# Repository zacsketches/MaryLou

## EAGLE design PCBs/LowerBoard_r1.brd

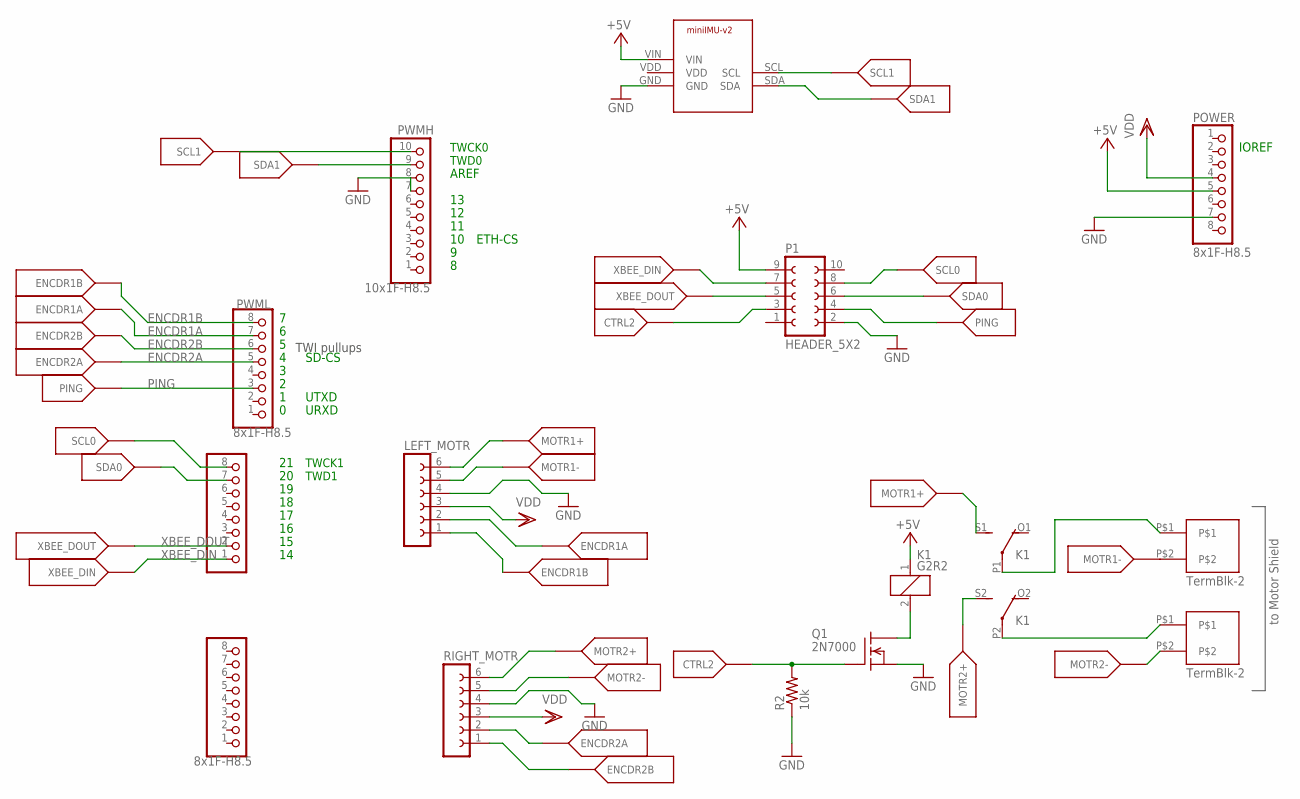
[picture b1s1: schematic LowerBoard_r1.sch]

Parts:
ANALOG: 8x1F-H8.5; 1X08
COMMS: PINHD-1X8; 1X08
K1: G2R2
LEFT_MOTR: FE06-1; FE06
P1: HEADER_5X2
POWER: 8x1F-H8.5; 1X08
PWMH: 10x1F-H8.5; 1X10
PWML: 8x1F-H8.5; 1X08
Q1: 2N7000; TO92
R2: 10k; RESISTOR_PKG
RIGHT_MOTR: FE06-1; FE06
U$5: POLOLU_MINIIMU9_V2; POLOLU_IMU9V2
U$11: motor1; TB2_PKG
U$12: TB2; TB2_PKG

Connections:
+5V: K1.1, P1.9, POWER.5, U$5.VIN
CTRL2: P1.3, Q1.G, R2.2
ENCDR1A: LEFT_MOTR.2, PWML.7
ENCDR1B: LEFT_MOTR.1, PWML.8
ENCDR2A: PWML.5, RIGHT_MOTR.2
ENCDR2B: PWML.6, RIGHT_MOTR.1
GND: LEFT_MOTR.4, P1.2, POWER.7, PWMH.7, Q1.S, R2.1, RIGHT_MOTR.4, U$5.GND
MOTR1+: K1.S1 (S), LEFT_MOTR.6
MOTR1-: LEFT_MOTR.5, U$11.P$2
MOTR2+: K1.S2 (S), RIGHT_MOTR.6
MOTR2-: RIGHT_MOTR.5, U$12.P$2
unnamed: K1.P1, U$11.P$1
unnamed: K1.P2, U$12.P$1
unnamed: K1.2, Q1.D
PING: P1.4, PWML.3
SCL: PWMH.10, U$5.SCL
SCL0: COMMS.8, P1.8
SDA: PWMH.9, U$5.SDA
SDA0: COMMS.7, P1.6
VDD: LEFT_MOTR.3, POWER.4, RIGHT_MOTR.3
XBEE_DIN: COMMS.1, P1.7
XBEE_DOUT: COMMS.2, P1.5

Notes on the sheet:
TWI pullups
TWCK1
TWD1
IOREF
TWCK0
TWD0
AREF
SD-CS
UTXD
URXD
ETH-CS
to Motor Shield

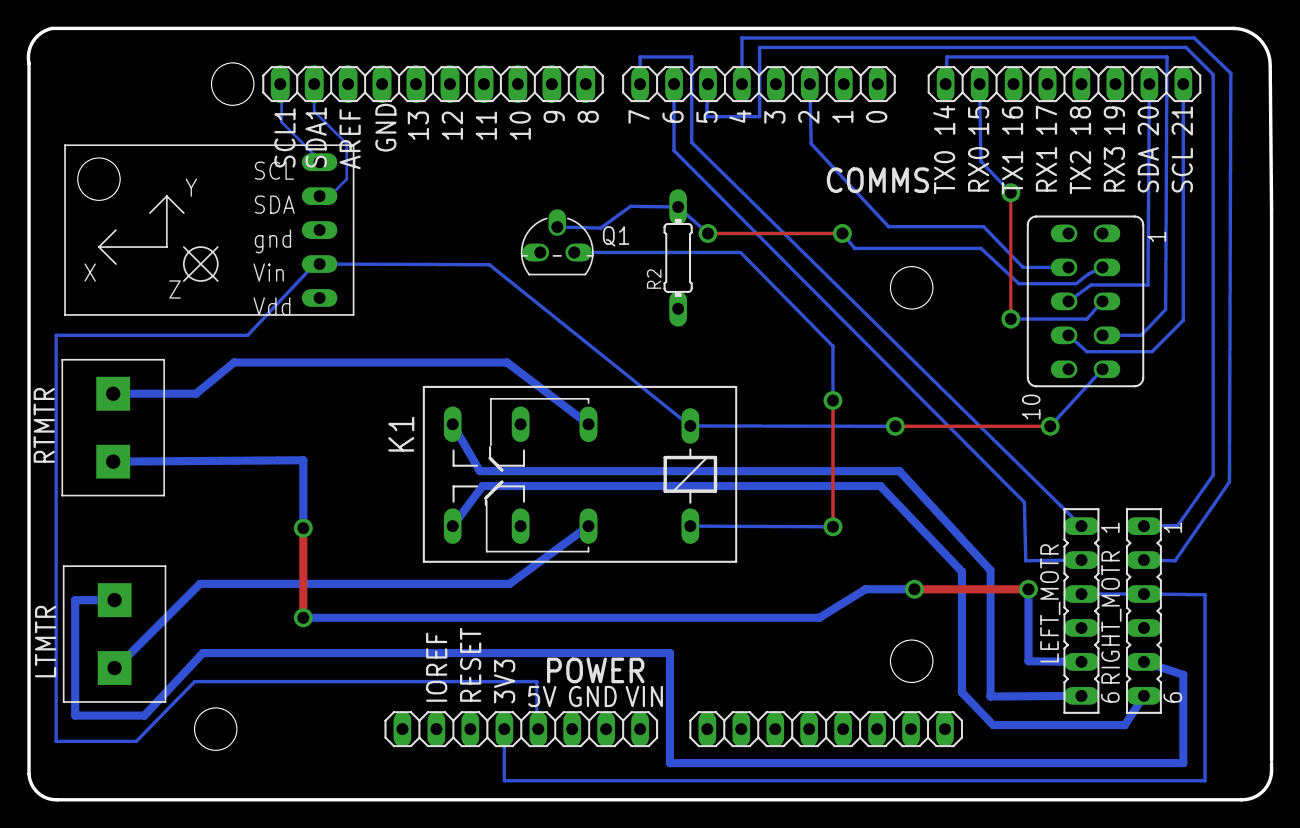
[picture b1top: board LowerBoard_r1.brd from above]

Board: 2 copper layers, 93.0 x 57.7 mm, 15 parts (0 on the bottom side), 22 nets.

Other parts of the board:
DRILEGEND: DRILEGEND

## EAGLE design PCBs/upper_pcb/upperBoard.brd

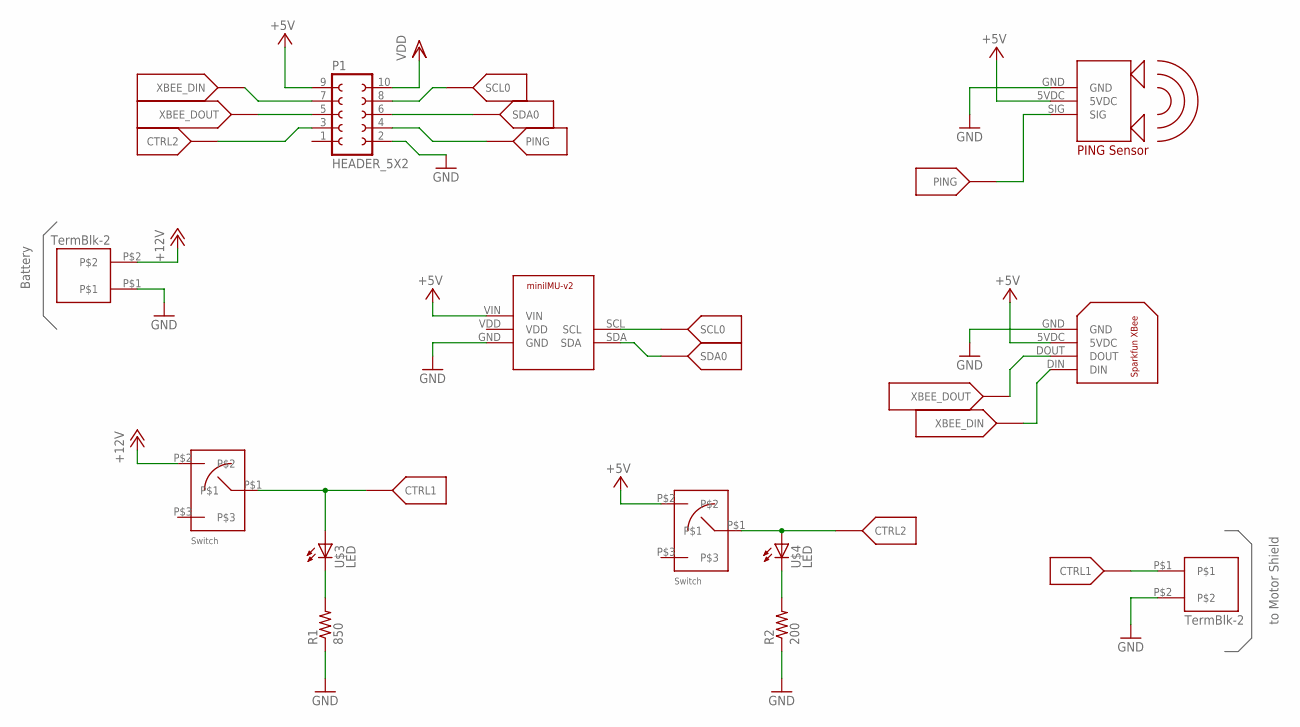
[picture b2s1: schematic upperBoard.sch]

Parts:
P1: HEADER_5X2
R1: 850; RESISTOR_PKG
R2: 200; RESISTOR_PKG
U$1, U$2: SWITCH-SPST
U$3, U$4: LED; LED_PKG
U$7: POLOLU_MINIIMU9_V2; POLOLU_IMU9V2
U$8: SPARKFUNXBEE
U$9: PARALLAX_PING; PING
U$16, U$18: TB2; TB2_PKG

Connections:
+5V: P1.9, U$2.P$2, U$7.VIN, U$8.5VDC, U$9.5VDC
+12V: U$1.P$2, U$16.P$2
CTRL1: U$1.P$1, U$3.A, U$18.P$1
CTRL2: P1.3, U$2.P$1, U$4.A
GND: P1.2, R1.1, R2.1, U$7.GND, U$8.GND, U$9.GND, U$16.P$1, U$18.P$2
unnamed: R1.2, U$3.K (C)
unnamed: R2.2, U$4.K (C)
PING: P1.4, U$9.SIG
SCL0: P1.8, U$7.SCL
SDA0: P1.6, U$7.SDA
VDD: P1.10
XBEE_DIN: P1.7, U$8.DIN
XBEE_DOUT: P1.5, U$8.DOUT

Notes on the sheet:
Battery
to Motor Shield

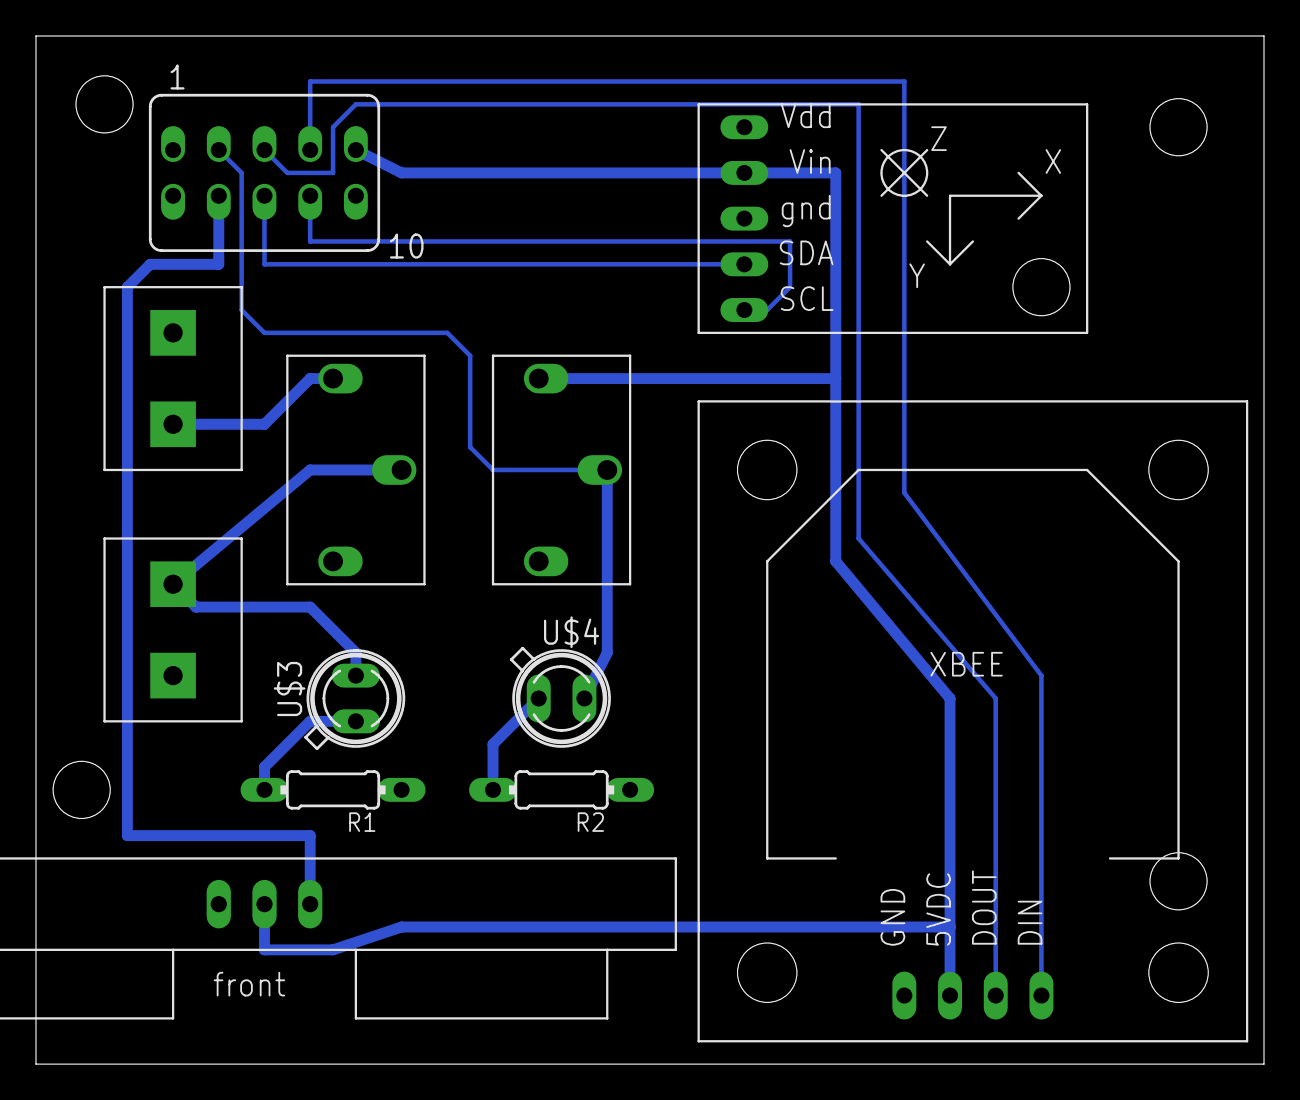
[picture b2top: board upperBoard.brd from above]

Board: 2 copper layers, 68.2 x 57.1 mm, 13 parts (0 on the bottom side), 12 nets.

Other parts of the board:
DRILEGEND: DRILEGEND

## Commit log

2014-10-08 added solidworks files to the project
2014-10-08 added Frame assembly and new Baseplate
    the new Frame assembly includes the mates for
    all the parts. The new Baseplate includes
    the mounting holes for the Neck.
2014-10-09 added table and neck drawing
2014-10-10 Created basic messaging strategy
2014-10-10 Added bill of materials
2014-10-14 major changes
    - Rebuilt file structure to seperate code from physical data
    and reference data
    - Wrote the first code in gyro_test to start working with Pololu
    IMU v2.
2014-10-14 gyro_test compiles...ready for testing e
2014-10-14 added base file for the final robot
2014-10-14 added conv to deg to the gyro test
2014-10-14 Added physical connections
2014-10-14 Added accel .pdf to datasheets
2014-10-15 Added link for IMU info
2014-10-15 Working accelerometer script
2014-10-15 correctd the units to degrees function
2014-10-15 Pitch regulator example added
2014-10-16 compiles...lot's of work still
    - I need to go back into my accel test and change the formula there
    so I get a signed value for pitch. I can't regulate the pitch
    from the gyro until I'm getting like signs from both devices.
2014-10-16 added app note for finding pitch
2014-10-16 used new pitch solution with a signed answer.
2014-10-16 Changed to direct calculation of pitch
    - An important change in this revision, I changed from a
    vector solution to pitch using dot products to a direct
    calculation of pitch using the technique described in
    Freescale App Note 3461.
2014-10-16 Removed unused variables
2014-10-16 Closed issue #1 - adde macro logging
2014-10-16 renamed file to better match its purpose
2014-10-16 Added refs to AN3461 and atan vs atan2
2014-10-16 Yahoo!!! Regulates gyro stability to +/- .3 deg
    - Tuned the PI controller and changed the sign for the
    error signal provide negative feedback.
2014-10-16 Added PI controller tuning reference
2014-10-16 added gyro system diagram to datasheets
2014-10-16 Fine tuned the gyro drift regulator...go with this for now.
2014-10-17 changed phi to theta for pitch variable
2014-10-17 updated System design
2014-10-17 Made a compatibility note at the top of the file
2014-10-17 updated System Design graphic
2014-10-22 working attitude computer
2014-10-22 Updated types for state vector message
2014-10-22 Added state vector process...needs testing
2014-10-23 Working state observer
2014-10-23 added deadband reference to datasheets
2014-10-23 added an MIT thesis on balancing robots and a dedband lab to datasheets
2014-10-23 minor change to LOG macro
2014-10-23 Added another balancing paper to datasheets
2014-10-23 Deadband comp added to the build notes
2014-10-23 updated system diagrams
    - included deadband compensator
    - added pointer and ref designations for subordinate objects
    - added notes for attitude computer
2014-10-24 Moment of Inertia plan for compound pendulums
2014-10-25 added Nise references and updated build notes
2014-10-25 Added pendulum equations of motion
2014-11-13 Added PCB files for lower board
2014-11-14 finished eagle file for lower PCB
2014-11-14 added PCB Cam file
2014-11-15 first atttempt to cut
2014-12-05 Added motor test
2014-12-10 updated accel test to due sec I2C port
2014-12-11 Added notes for finding the moment of inertia
2014-12-11 Added notes for Stanford dynamics
2014-12-12 pcb info for top and bottom
2014-12-12 updated accel test to reflect accurate axis alignment
2014-12-12 Printed version of top circuit board
2014-12-13 Updated all dev scripts to the build
2014-12-13 Two important changes
    - Added Simpson rule integration for the gyro. This calculation
    should provide a slight improvement over the trap z integration
    I was previously running. This effectively allows me to run
    a filter over four steps of data.
    - I corrected errrors in the PI controller to that were eliminating
    the input from the I component. I also changed the PI controller
2014-12-14 added more dev sketches
2014-12-14 Multiple changes to move the project ahead
    Added three dev sketches
    - quadrature_decoder uses the raw addresses of the encoders
    to ensure I can count movement on the installed equipment
    - basic_gw_quadrature wraps the success in the basic
    quadrature in the glow worm framework and validates that it
    works. You have to turn the wheels by hand for these sketches.
2014-12-14 Added the config file to the repo.
    I need to add a link in the actual Arduino/library folder so that
    this config file is updated and used.
2014-12-16 Several Changes
    - Added an image of our whiteboard to the Datasheets folder
    of our work to get to the running Simpson rule integration
    we implemented.
    - Working through the details on the exec file...lots more to
    do here.
    - Added more detail the Robot Config file
2014-12-16 Updated constants
2014-12-16 Added a print statement before the delay
